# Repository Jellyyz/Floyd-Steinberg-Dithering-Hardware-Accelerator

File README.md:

# ECE445 Spring 2023, Team 29: Portable Thermal Printer

https://www.youtube.com/watch?v=ZJqiJV0miBM

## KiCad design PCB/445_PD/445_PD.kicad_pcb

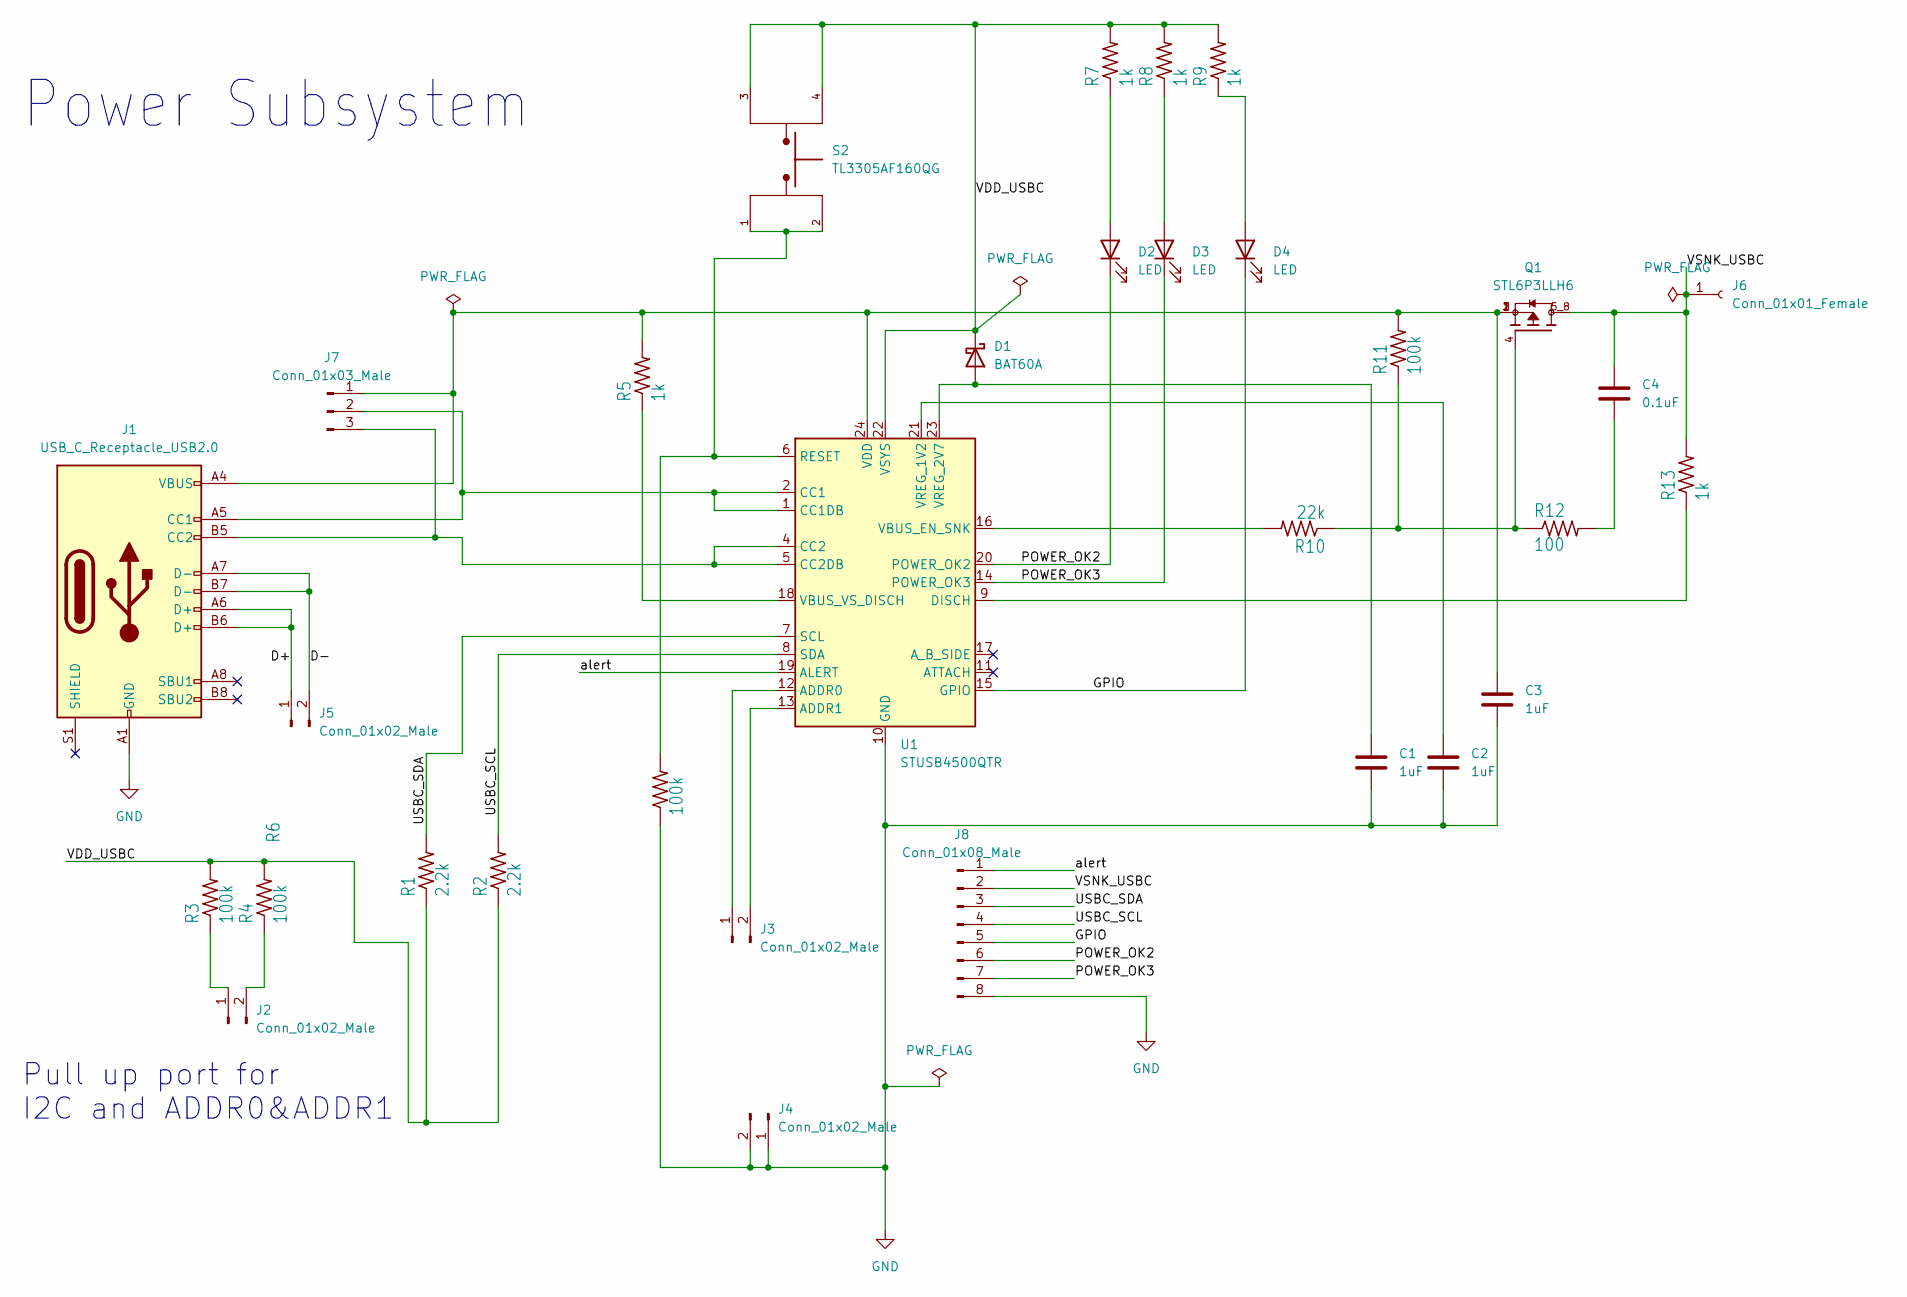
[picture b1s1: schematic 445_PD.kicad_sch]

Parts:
C1, C2, C3: 1uF; C_0805_2012Metric_Pad1.18x1.45mm_HandSolder
C4: 0.1uF; C_0805_2012Metric_Pad1.18x1.45mm_HandSolder
D1: BAT60A; D_SOD-323
D2, D3, D4: LED; LED_0603_1608Metric_Pad1.05x0.95mm_HandSolder
J1: USB_C_Receptacle_USB2.0; USB_C_Receptacle_GCT_USB4105-xx-A_16P_TopMnt_Horizontal
J2, J3, J4, J5: Conn_01x02_Male; PinHeader_1x02_P2.54mm_Vertical
J6: Conn_01x01_Female; PinHeader_1x01_P2.54mm_Vertical
J7: Conn_01x03_Male; PinHeader_1x03_P2.54mm_Vertical
J8: Conn_01x08_Male; PinHeader_1x08_P2.54mm_Vertical
Q1: STL6P3LLH6; TRANS_STL6P3LLH6; PARTREV 4
R1, R2: 2.2k; R_0805_2012Metric_Pad1.20x1.40mm_HandSolder
R3, R4, R6, R11: 100k; R_0805_2012Metric_Pad1.20x1.40mm_HandSolder
R5, R7, R8, R9, R13: 1k; R_0805_2012Metric_Pad1.20x1.40mm_HandSolder
R10: 22k; R_0805_2012Metric_Pad1.20x1.40mm_HandSolder
R12: 100; R_0805_2012Metric_Pad1.20x1.40mm_HandSolder
S2: TL3305AF160QG; SW_TL3305AF160QG; PARTREV C
U1: STUSB4500QTR; QFN-24-1EP_4x4mm_P0.5mm_EP2.7x2.7mm

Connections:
/D+: J1.A6 (D+), J1.B6 (D+), J5.1
/D-: J1.A7 (D-), J1.B7 (D-), J5.2
/GPIO: D4.1 (K), J8.5, U1.15 (GPIO)
/POWER_OK2: D2.1 (K), J8.6, U1.20 (POWER_OK2)
/POWER_OK3: D3.1 (K), J8.7, U1.14 (POWER_OK3)
/USBC_SCL: J8.4, R2.2, U1.8 (SDA)
/USBC_SDA: J8.3, R1.2, U1.7 (SCL)
/VDD_USBC: D1.1 (K), R1.1, R2.1, R3.2, R4.2, R7.2, R8.2, R9.2, S2.3, S2.4, U1.22 (VSYS)
/VSNK_USBC: C4.1, J6.1, J8.2, Q1.5_8, R13.2
/alert: J8.1, U1.19 (ALERT)
GND: C1.2, C2.2, C3.2, J1.A1 (GND), J1.A12 (GND), J1.B1 (GND), J1.B12 (GND), J4.1, J4.2, J8.8, R6.1, U1.10 (GND), U1.25 (GND)
unnamed: C1.1, D1.2 (A), U1.23 (VREG_2V7)
unnamed: C2.1, U1.21 (VREG_1V2)
unnamed: C3.1, J1.A4 (VBUS), J1.A9 (VBUS), J1.B4 (VBUS), J1.B9 (VBUS), J7.1, Q1.1, Q1.2, Q1.3, R5.2, R11.2, U1.24 (VDD)
unnamed: C4.2, R12.2
unnamed: D2.2 (A), R7.1
unnamed: D3.2 (A), R8.1
unnamed: D4.2 (A), R9.1
unnamed: J1.A5 (CC1), J7.2, U1.1 (CC1DB), U1.2 (CC1)
unnamed: J1.B5 (CC2), J7.3, U1.4 (CC2), U1.5 (CC2DB)
unnamed: J2.1, R3.1
unnamed: J2.2, R4.1
unnamed: J3.1, U1.12 (ADDR0)
unnamed: J3.2, U1.13 (ADDR1)
unnamed: Q1.4, R10.1, R11.1, R12.1
unnamed: R5.1, U1.18 (VBUS_VS_DISCH)
unnamed: R6.2, S2.1, S2.2, U1.6 (RESET)
unnamed: R10.2, U1.16 (VBUS_EN_SNK)
unnamed: R13.1, U1.9 (DISCH)

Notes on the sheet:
Power Subsystem
Pull up port for I2C and ADDR0&ADDR1

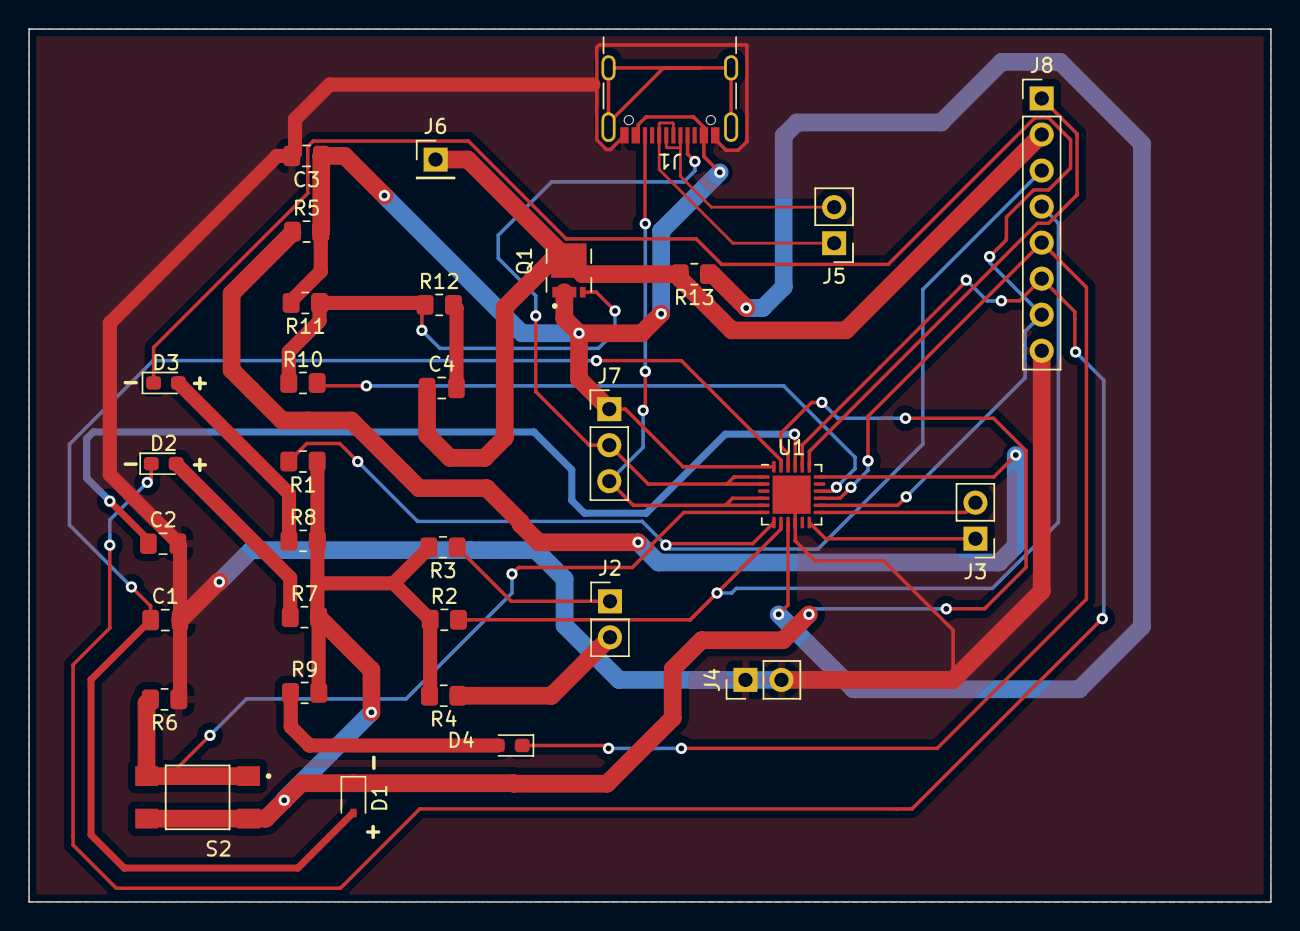
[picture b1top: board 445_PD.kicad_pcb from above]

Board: 2 copper layers, 87.5 x 61.5 mm, 32 parts (0 on the bottom side), 29 nets.

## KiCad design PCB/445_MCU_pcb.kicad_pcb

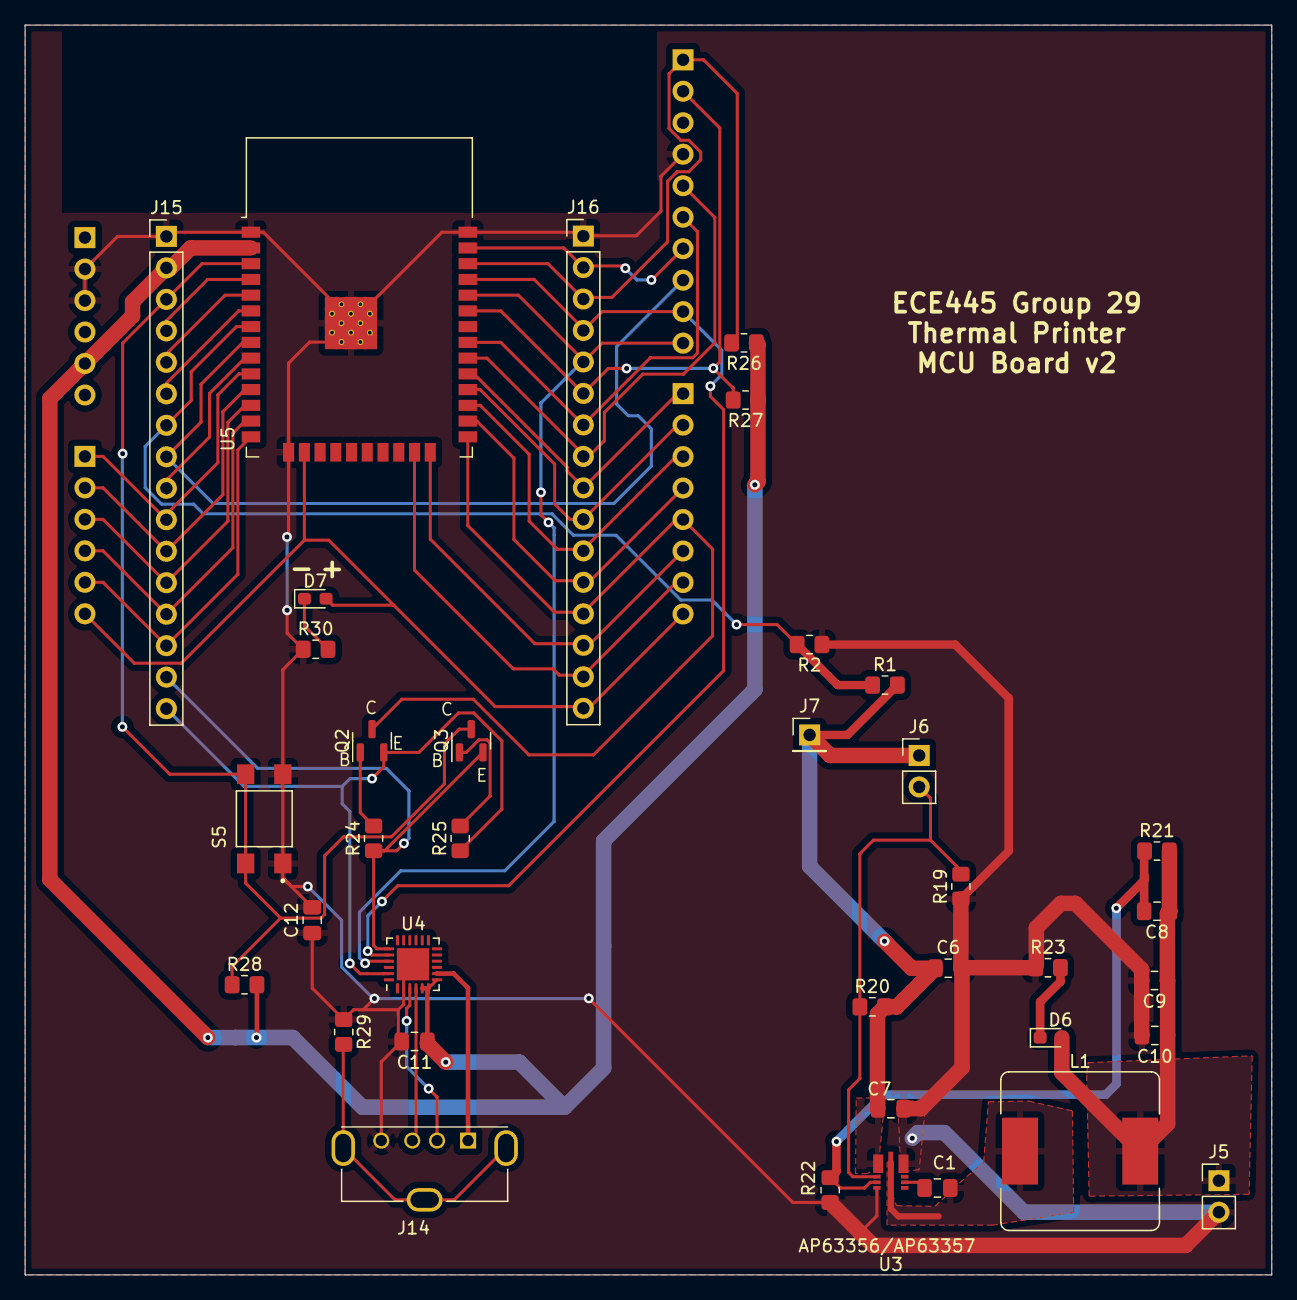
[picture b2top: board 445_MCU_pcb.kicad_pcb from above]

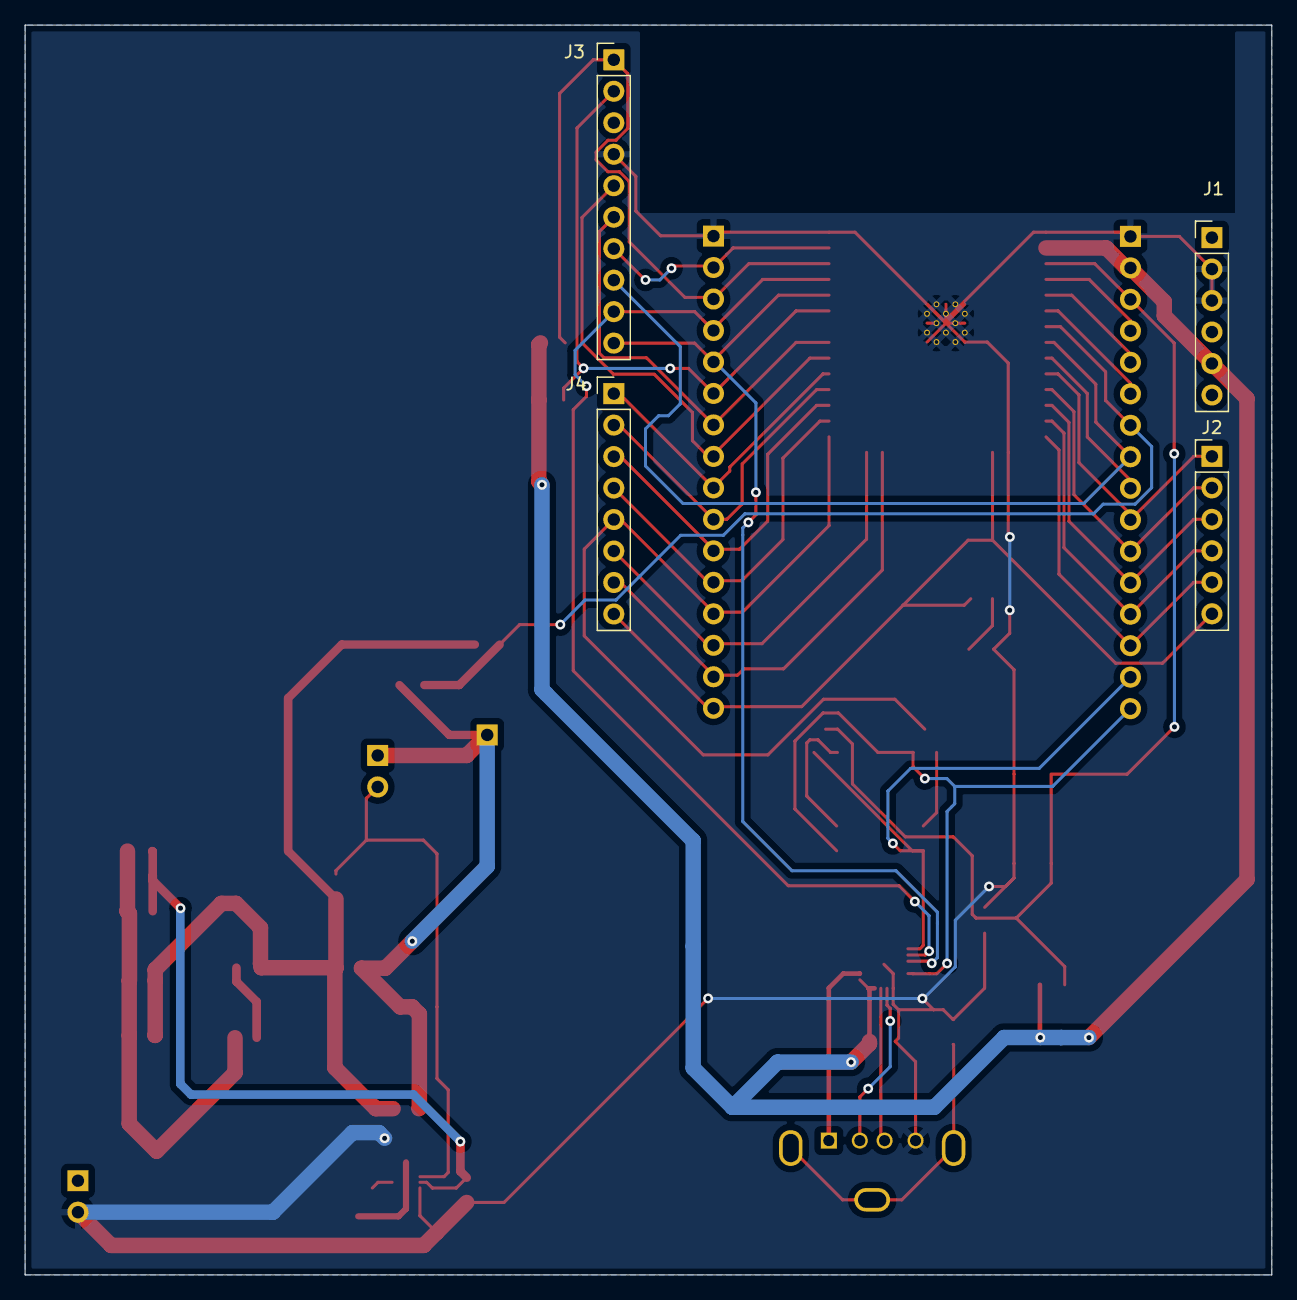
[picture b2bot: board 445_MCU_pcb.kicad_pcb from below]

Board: 2 copper layers, 100.6 x 100.8 mm, 41 parts (4 on the bottom side), 45 nets.

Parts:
C1: 0.1uF; C_0805_2012Metric_Pad1.18x1.45mm_HandSolder
C6, C7, C12: 4.7uF; C_0805_2012Metric_Pad1.18x1.45mm_HandSolder
C8: 47pF; C_0805_2012Metric_Pad1.18x1.45mm_HandSolder
C9, C10: 22uF; C_0805_2012Metric_Pad1.18x1.45mm_HandSolder
C11: 10uF; C_0805_2012Metric_Pad1.18x1.45mm_HandSolder
D6, D7: LED; LED_0603_1608Metric_Pad1.05x0.95mm_HandSolder
J1, J2: Conn_01x06_Male; PinHeader_1x06_P2.54mm_Vertical
J3: Conn_01x10_Male; PinHeader_1x10_P2.54mm_Vertical
J4: Conn_01x08_Male; PinHeader_1x08_P2.54mm_Vertical
J5, J6: Conn_01x02_Male; PinHeader_1x02_P2.54mm_Vertical
J7: Conn_01x01_Female; PinHeader_1x01_P2.54mm_Vertical
J14: USB_A; USB_A_Molex_105057_Vertical
J15, J16: Conn_01x16_Female; PinHeader_1x16_P2.54mm_Vertical
L1: 6.8uH; L_Bourns_SRR1260
Q2, Q3: MMBT5550L; SOT-23
R1, R2, R29: 100k; R_0805_2012Metric_Pad1.20x1.40mm_HandSolder
R19: 22k; R_0805_2012Metric_Pad1.20x1.40mm_HandSolder
R20: 93.1k; R_0805_2012Metric_Pad1.20x1.40mm_HandSolder
R21: 220k; R_0805_2012Metric_Pad1.20x1.40mm_HandSolder
R22: 41.2k; R_0805_2012Metric_Pad1.20x1.40mm_HandSolder
R23, R26, R27: 2.2k; R_0805_2012Metric_Pad1.20x1.40mm_HandSolder
R24, R25, R28: 10k; R_0805_2012Metric_Pad1.20x1.40mm_HandSolder
R30: 1k; R_0805_2012Metric_Pad1.20x1.40mm_HandSolder
S5: TL3305AF160QG; SW_TL3305AF160QG
U3: AP63356/AP63357; AP63357DV-7
U4: CP2104; QFN-24-1EP_4x4mm_P0.5mm_EP2.6x2.6mm
U5: ESP32-WROOM-32

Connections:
3.3V1: C11.1, J1.5, J15.2, R26.1, R27.1, R28.2, U4.5 (VIO), U4.6 (VDD), U4.7 (REGIN), U5.2 (VDD)
/7_4VIn: C6.1, C7.1, J6.1, J7.1, R1.2, R20.2, U3.1 (VIN)
/DTR: J15.16, Q2.2 (E), R25.1, U4.23 (~DTR)
/EN: J6.2, R19.2, R20.1, U3.2 (EN)
/IO0: J4.5, J16.13, Q2.3 (C), U5.25 (IO0)
/IO1/UART0_TX: J3.9, J16.4, U4.20 (RXD), U5.35 (TXD0/IO1)
/IO2: J4.6, J16.14, U5.24 (IO2)
/IO3/UART0_RX: J3.10, J16.5, U4.21 (TXD), U5.34 (RXD0/IO3)
/IO4/A2_C0: J4.4, J16.12, U5.26 (IO4)
/IO5: J4.1, J16.9, U5.29 (IO5)
/IO12/A2_C5: J2.5, J15.14, U5.14 (IO12)
/IO13/A2_C4: D7.2 (A), J2.6, J4.8, J16.16, U5.16 (IO13)
/IO14/A2_C6: J2.4, J15.13, U5.13 (IO14)
/IO15/A2_C3: J4.7, J16.15, U5.23 (IO15)
/IO16/UART2_RX: J4.3, J16.11, U5.27 (IO16)
/IO17/UART2_TX: J4.2, J16.10, U5.28 (IO17)
/IO18/SCLK: J3.5, J16.8, U5.30 (IO18)
/IO19/MISO: J3.6, J16.7, U5.31 (IO19)
/IO21/SDA: J3.2, J16.6, R27.2, U5.33 (IO21)
/IO22/SCL: J3.1, J16.3, R26.2, U5.36 (IO22)
/IO23/MOSI: J3.7, J16.2, U5.37 (IO23)
/IO25/A2_C8: J2.1, J15.10, U5.10 (IO25)
/IO26/A2_c9: J2.2, J15.11, U5.11 (IO26)
/IO27/A2_C7: J2.3, J15.12, U5.12 (IO27)
/IO32/SPI_SS: J3.8, J15.8, U5.8 (IO32)
/IO33/SPI_CLK: J15.9, U5.9 (IO33)
/IO34/IN_ONLY: J15.6, U5.6 (IO34)
/IO35/IN_ONLY: J15.7, R1.1, R2.2, U5.7 (IO35)
/RST: J15.3, Q3.3 (C), R28.1, S5.3, S5.4, U5.3 (EN)
/RTS: J15.15, Q3.2 (E), R24.1, U4.19 (~RTS)
/SENSOR_VN/IO39: J15.5, U5.5 (SENSOR_VN)
/SENSOR_VP/IO36: J15.4, U5.4 (SENSOR_VP)
GND: C6.2, C7.2, C9.2, C10.2, C11.2, C12.1, C12.2, J1.2, J1.3, J3.4, J5.2, J14.4 (GND), J15.1, J16.1, R2.1, R19.1, R22.1, R23.1, R29.1, R30.1, S5.1, S5.2, U3.4 (COMP), U3.8 (GND), U4.2 (GND), U4.25 (GND), U5.1 (GND), U5.15 (GND), U5.38 (GND), U5.39 (GND)
unnamed: C1.1, U3.6 (BST)
unnamed: C1.2, L1.1, U3.9 (SW)
unnamed: C8.2, R21.1, R22.2, U3.3 (FB)
unnamed: D6.1 (K), R23.2
unnamed: D7.1 (K), R30.2
unnamed: J14.1 (VBUS), U4.8 (VBUS)
unnamed: J14.2 (D-), U4.3 (D+)
unnamed: J14.3 (D+), U4.4 (D-)
unnamed: J14.5 (Shield), R29.2
unnamed: Q2.1 (B), R24.2
unnamed: Q3.1 (B), R25.2
TO_FPGA_USB: C8.1, C9.1, C10.1, D6.2 (A), J5.1, L1.2, R21.2

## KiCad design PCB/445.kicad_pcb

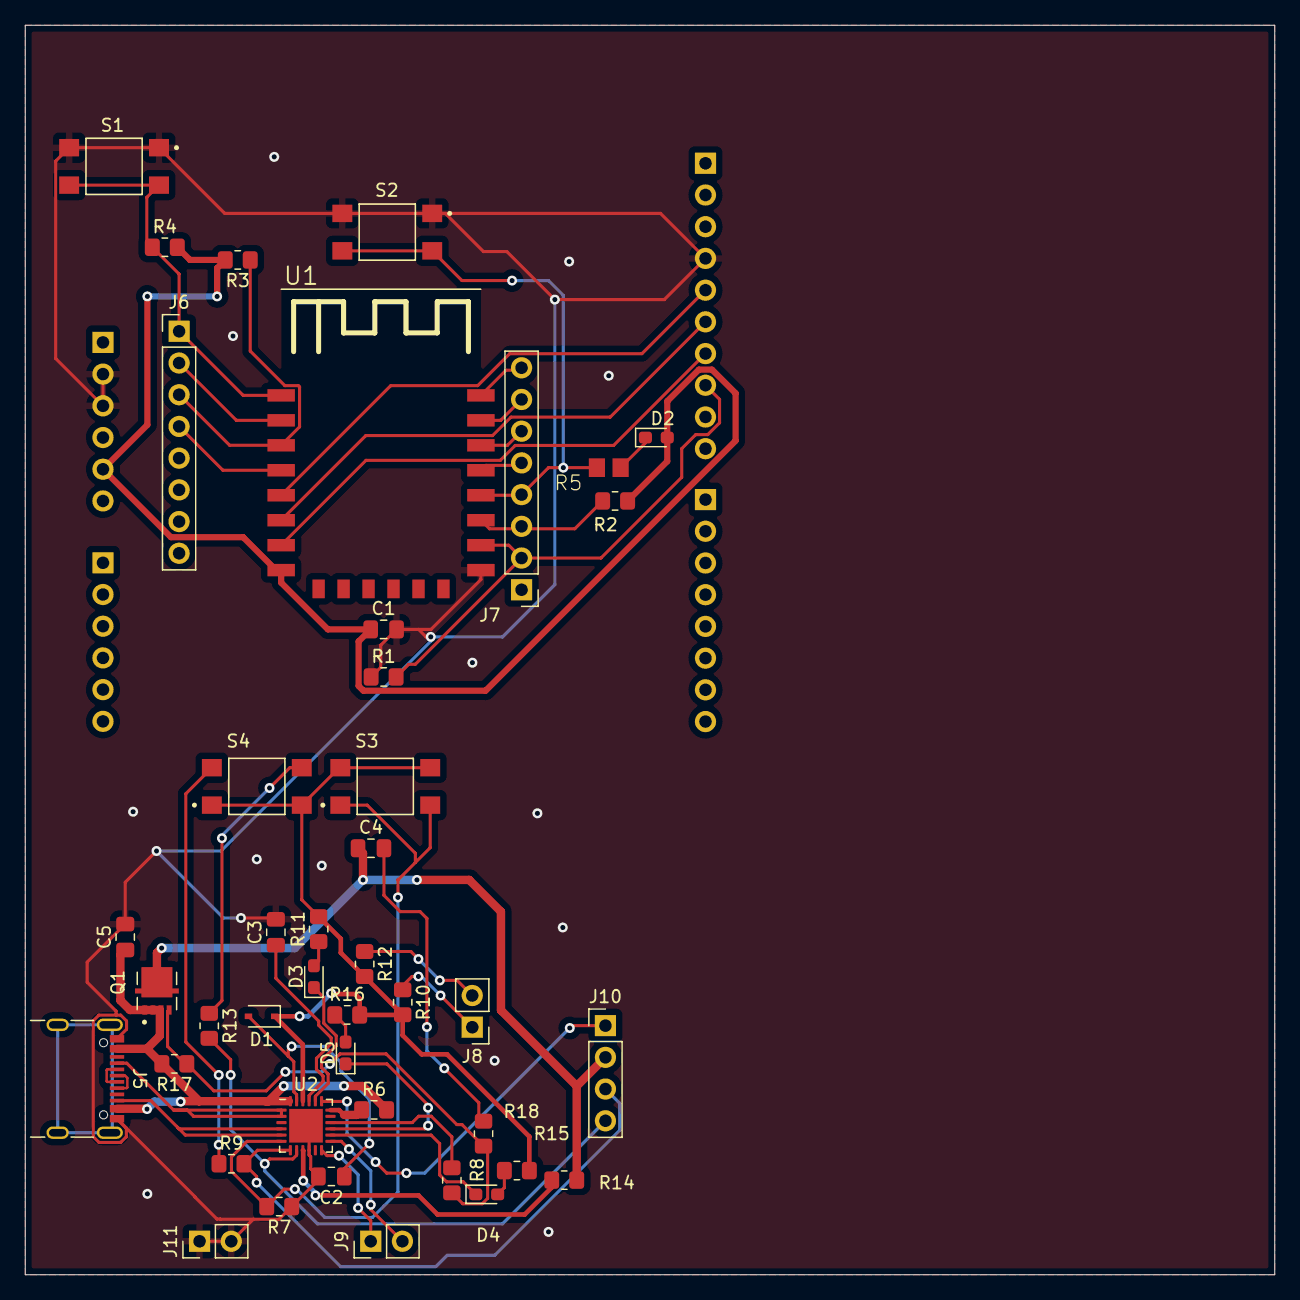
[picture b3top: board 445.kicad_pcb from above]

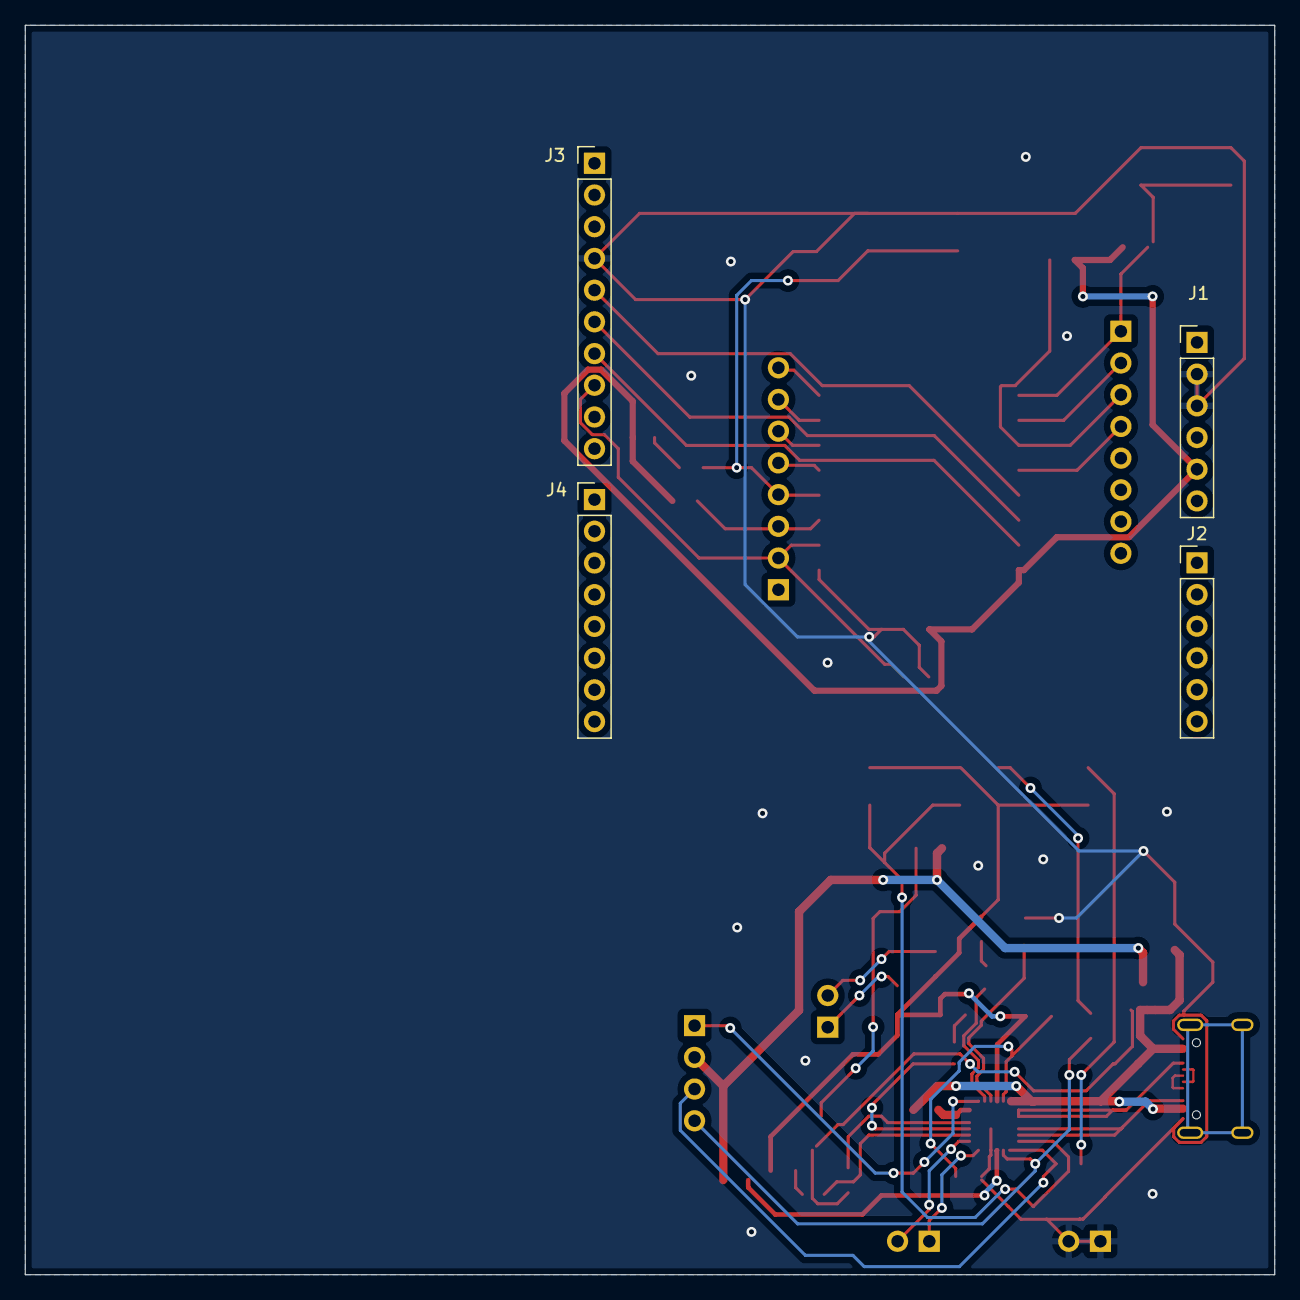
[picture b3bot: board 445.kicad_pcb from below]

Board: 2 copper layers, 100.1 x 100.1 mm, 46 parts (4 on the bottom side), 47 nets.

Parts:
C1, C2, C3, C5: 1uF; C_0805_2012Metric_Pad1.18x1.45mm_HandSolder
C4: 0.1uF; C_0805_2012Metric_Pad1.18x1.45mm_HandSolder
D1: BAT60A; D_SOD-323
D2, D3, D4, D5: LED; LED_0603_1608Metric_Pad1.05x0.95mm_HandSolder
J1, J2: Conn_01x06_Male; PinHeader_1x06_P2.54mm_Vertical
J3: Conn_01x10_Male; PinHeader_1x10_P2.54mm_Vertical
J4: Conn_01x08_Male; PinHeader_1x08_P2.54mm_Vertical
J5: USB_C_Receptacle_USB2.0; USB_C_Receptacle_GCT_USB4105-xx-A_16P_TopMnt_Horizontal
J6, J7: Conn_01x08_Female; PinHeader_1x08_P2.54mm_Vertical
J8, J9, J11: Conn_01x02_Male; PinHeader_1x02_P2.54mm_Vertical
J10: Conn_01x04_Male; PinHeader_1x04_P2.54mm_Vertical
Q1: STL6P3LLH6; TRANS_STL6P3LLH6
R1, R2, R3, R4: 10k; R_0805_2012Metric_Pad1.20x1.40mm_HandSolder
R5: R-US_R0805; R0805
R6, R11, R14, R15, R16: 1k; R_0805_2012Metric_Pad1.20x1.40mm_HandSolder
R7, R10, R12, R17: 100k; R_0805_2012Metric_Pad1.20x1.40mm_HandSolder
R8: 22k; R_0805_2012Metric_Pad1.20x1.40mm_HandSolder
R9, R13: 2.2k; R_0805_2012Metric_Pad1.20x1.40mm_HandSolder
R18: 100; R_0805_2012Metric_Pad1.20x1.40mm_HandSolder
S1, S2, S3, S4: TL3305AF160QG; SW_TL3305AF160QG
U1: ESP-12F
U2: STUSB4500QTR; QFN-24-1EP_4x4mm_P0.5mm_EP2.7x2.7mm

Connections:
/3.3V1: C1.1, D2.2 (A), J1.5, R2.2, R3.2, R4.2, U1.8 (VCC)
/ADC: J6.2, U1.2 (ADC)
/D+: J5.A6 (D+), J5.B6 (D+)
/D-: J5.A7 (D-), J5.B7 (D-)
/ESP_EN: J6.3, R3.1, U1.3 (CH_PD)
/ESP_RST: J6.1, R4.1, S1.3, S1.4, U1.1 (REST)
/GPIO0: J7.4, R5.1, S2.3, S2.4, U1.18 (GPIO0)
/GPIO4: J7.5, U1.19 (GPIO04)
/GPIO5: J7.6, U1.20 (GPIO05)
/GPIO15/SS: J3.8, J7.2, R1.2, U1.16 (GPIO15)
/GPIO16: J6.4, U1.4 (GPIO16)
/LED_GPIO2_BOOT: J7.3, R2.1, U1.17 (GPIO02)
/MISO: J3.6, U1.6 (GPIO12)
/MOSI: J3.7, U1.7 (GPIO13)
/RX: J7.7, U1.21 (RXD)
/SCLK: J3.5, U1.5 (GPIO14)
/TX: J7.8, U1.22 (TXD)
/USBC_SCL: J10.4, R13.2, U2.8 (SDA)
/USBC_SDA: J10.3, R9.2, U2.7 (SCL)
/VDD_USBC: D1.1 (K), R10.2, R11.2, R12.2, R15.2, R16.2, S3.3, S3.4, S4.1, S4.2, U2.22 (VSYS)
/VSNK_USBC: C4.1, J10.2, Q1.5_8, R14.2
/alert: J10.1, U2.19 (ALERT)
GND: C1.2, C2.2, C3.2, C5.2, J1.2, J1.3, J3.4, J5.A1 (GND), J5.A12 (GND), J5.B1 (GND), J5.B12 (GND), J11.1, J11.2, R1.1, R7.1, S1.1, S1.2, S2.1, S2.2, U1.15 (GND), U2.10 (GND), U2.25 (GND)
unnamed: C2.1, D1.2 (A), U2.23 (VREG_2V7)
unnamed: C3.1, U2.21 (VREG_1V2)
unnamed: C4.2, R18.2
unnamed: C5.1, J5.A4 (VBUS), J5.A9 (VBUS), J5.B4 (VBUS), J5.B9 (VBUS), Q1.1, Q1.2, Q1.3, R6.2, R17.2, U2.24 (VDD)
unnamed: D2.1 (K), R5.2
unnamed: D3.1 (K), U2.20 (POWER_OK2)
unnamed: D3.2 (A), R11.1
unnamed: D4.1 (K), U2.14 (POWER_OK3)
unnamed: D4.2 (A), R15.1
unnamed: D5.1 (K), U2.15 (GPIO)
unnamed: D5.2 (A), R16.1
unnamed: J5.A5 (CC1), U2.1 (CC1DB), U2.2 (CC1)
unnamed: J5.B5 (CC2), U2.4 (CC2), U2.5 (CC2DB)
unnamed: J8.1, R10.1
unnamed: J8.2, R12.1
unnamed: J9.1, U2.12 (ADDR0)
unnamed: J9.2, U2.13 (ADDR1)
unnamed: Q1.4, R8.1, R17.1, R18.1
unnamed: R6.1, U2.18 (VBUS_VS_DISCH)
unnamed: R7.2, S3.1, S3.2, U2.6 (RESET)
unnamed: R8.2, U2.16 (VBUS_EN_SNK)
unnamed: R9.1, S4.3
unnamed: R13.1, S4.4
unnamed: R14.1, U2.9 (DISCH)

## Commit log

2023-01-24 adding RFA
2023-01-25 Fixed typos, moved text, added subsystem skeletons
2023-01-25 1/25
2023-01-25 Meeting update
2023-01-25 Meeting final markdown
2023-01-25 More complexity added
2023-01-25 Fixed MCU line
2023-01-25 Added based on TA's suggestions
2023-01-26 RFA 1/25
2023-01-26 RFA 1/25 v2
2023-02-04 Added a little bit for Proposal
2023-02-04 Added generic notebook directory
2023-02-05 changed proposal.md
2023-02-06 Updated Proposal part 1
2023-02-06 Formatted - rmv'd whitespace
2023-02-07 added basic hdl
2023-02-07 adding gally's notebook 2/7
2023-02-07 Synchronize Proposal, add Notebook
2023-02-07 kevin notebook update
    copied everything over to github notebook + added new entry
2023-02-07 safety & sopme fpga proposal
2023-02-07 Risk Analysis of server (Computer Security)
2023-02-07 Merged
2023-02-08 added new block diagram
2023-02-08 part 1 of high level requirements
2023-02-09 Updated proposal
2023-02-09 Noted my notebook
2023-02-09 adding visual aid
2023-02-09 Minor fixes to the diagram
2023-02-09 Updated image processing diagram
2023-02-09 proposal final?
2023-02-09 updated block diagram
2023-02-09 single line error
2023-02-09 Almost done proposal
2023-02-09 Fixed weird formatting
2023-02-09 fixed proposal
2023-02-09 Fixed quotation marks formatting
2023-02-10 final changes
2023-02-10 issues with converting to pdf
2023-02-10 Added PDF for af4667b... commit
2023-02-12 HDL code start 2/11
2023-02-13 added some more control unit
2023-02-13 baseline image unit done
2023-02-13 feb 13 notebook
2023-02-14 Added .sch and etc.
2023-02-14 Updated journal to Feb. 14
2023-02-15 Updated journal to Feb. 15
2023-02-16 Updated schematic
2023-02-16 team contract upload
2023-02-17 Started Team Contract & Design Document
2023-02-17 Fixed reference coloring
2023-02-18 Updated journal to 2/17/2023
2023-02-18 Attempted to fill in some design details
2023-02-19 added fixes to team contract
2023-02-19 Small fixes and formatting fixes
2023-02-19 Small additions to R&V, descriptions
2023-02-22 add final team contract and some hdl
2023-02-22 final team contract final
2023-02-24 design document + datasheets + updated block diagram
2023-02-24 Added non-PCB files for MCU breakout board
2023-03-01 Recorded stuff to be elaborated later
2023-03-10 Filled in template
2023-03-10 march 9th pushing schematic and v2 proposal
2023-03-10 Add slave
2023-03-10 Added slave image
2023-03-11 Added basic MCU-FPGA SPI test code
2023-03-11 Added READMEs
2023-03-11 Added compatible C++ implementation... unsure correctness
2023-03-12 Added basic Django to start testing server->mcu->fpga->mcu
2023-03-13 Updated notebook (rough)
2023-03-13 Rough descriptions
2023-03-13 Renamed HexdriverOverload module
2023-03-13 Added updated HDL
2023-03-13 Updated SPI Test 1 top level to adv.
2023-03-14 Added previous useful sketches
2023-03-15 Added SW imp update
2023-03-15 Added test HDL
2023-03-15 Updated TopLevel
2023-03-15 synthesizable hdl
2023-03-16 Added server -> MCU -> server testcode (valid for small imgs)
2023-03-16 Updated notebook
2023-03-16 Added software implementation that is run on PC
2023-03-17 testing memory
2023-03-17 cleaned up hdl folder
2023-03-18 added testing mem_block
2023-03-18 added basic handshaking between MCU and FPGA, yet to be tested
2023-03-20 working pixel iteration & basic testbench to support
2023-03-21 basic state machine working, have to get the actual image processing working, also updated my nb
2023-03-22 added hdl and hvl files
2023-03-22 somewhat working accelerator 3/22
2023-03-25 adding all before starting singleport
2023-03-25 started single port
2023-03-27 Updated software model
2023-03-30 add FPGA files 3/30
2023-04-11 Updated journal after inactivity
2023-04-11 Backtracking to fill journal
2023-04-11 Uploaded images to be used in journal.
2023-04-11 Images
2023-04-11 Apr. 4-5
2023-04-11 Apr. 2
2023-04-11 March 30-31 stuffs
2023-04-11 Upload printer page img.
2023-04-11 Test page upload
2023-04-11 March 27
2023-04-11 Upload img for journal
2023-04-11 March 24
2023-04-11 Upload sw hw images
2023-04-11 Update journal with vague descriptions...
2023-04-11 Major updates to the journal
2023-04-12 Upload SPI diagram
2023-04-12 4/11
2023-04-15 Current build of print-as-is system
2023-04-15 Updated notebook for multiple days
2023-04-17 Uploaded print test img from 4/14
2023-04-17 4/15/2023
2023-04-17 Added annotated img figure
2023-04-17 Visuals
2023-04-17 Visuals added for explanation
2023-04-17 Added untested looping SPI controller
2023-04-18 Broken code
2023-04-22 Variable size looping decent printing (prob.-based GET)
2023-04-24 added notebook update april/ final HDL
2023-04-25 Modified for variable dimensions
2023-04-25 Blah blah
2023-04-25 Notebook up to date
2023-04-26 Notebook 2nd to last or last
2023-05-02 Publish final versions that's flashed on PCB
2023-05-02 Video
2023-05-04 final notebook push??
2023-05-04 last commit, upload sample of frontend
2023-05-21 final push

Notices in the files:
parts and their libraries:
Copyright 2021 Accelerated Designs. All rights reserved.
